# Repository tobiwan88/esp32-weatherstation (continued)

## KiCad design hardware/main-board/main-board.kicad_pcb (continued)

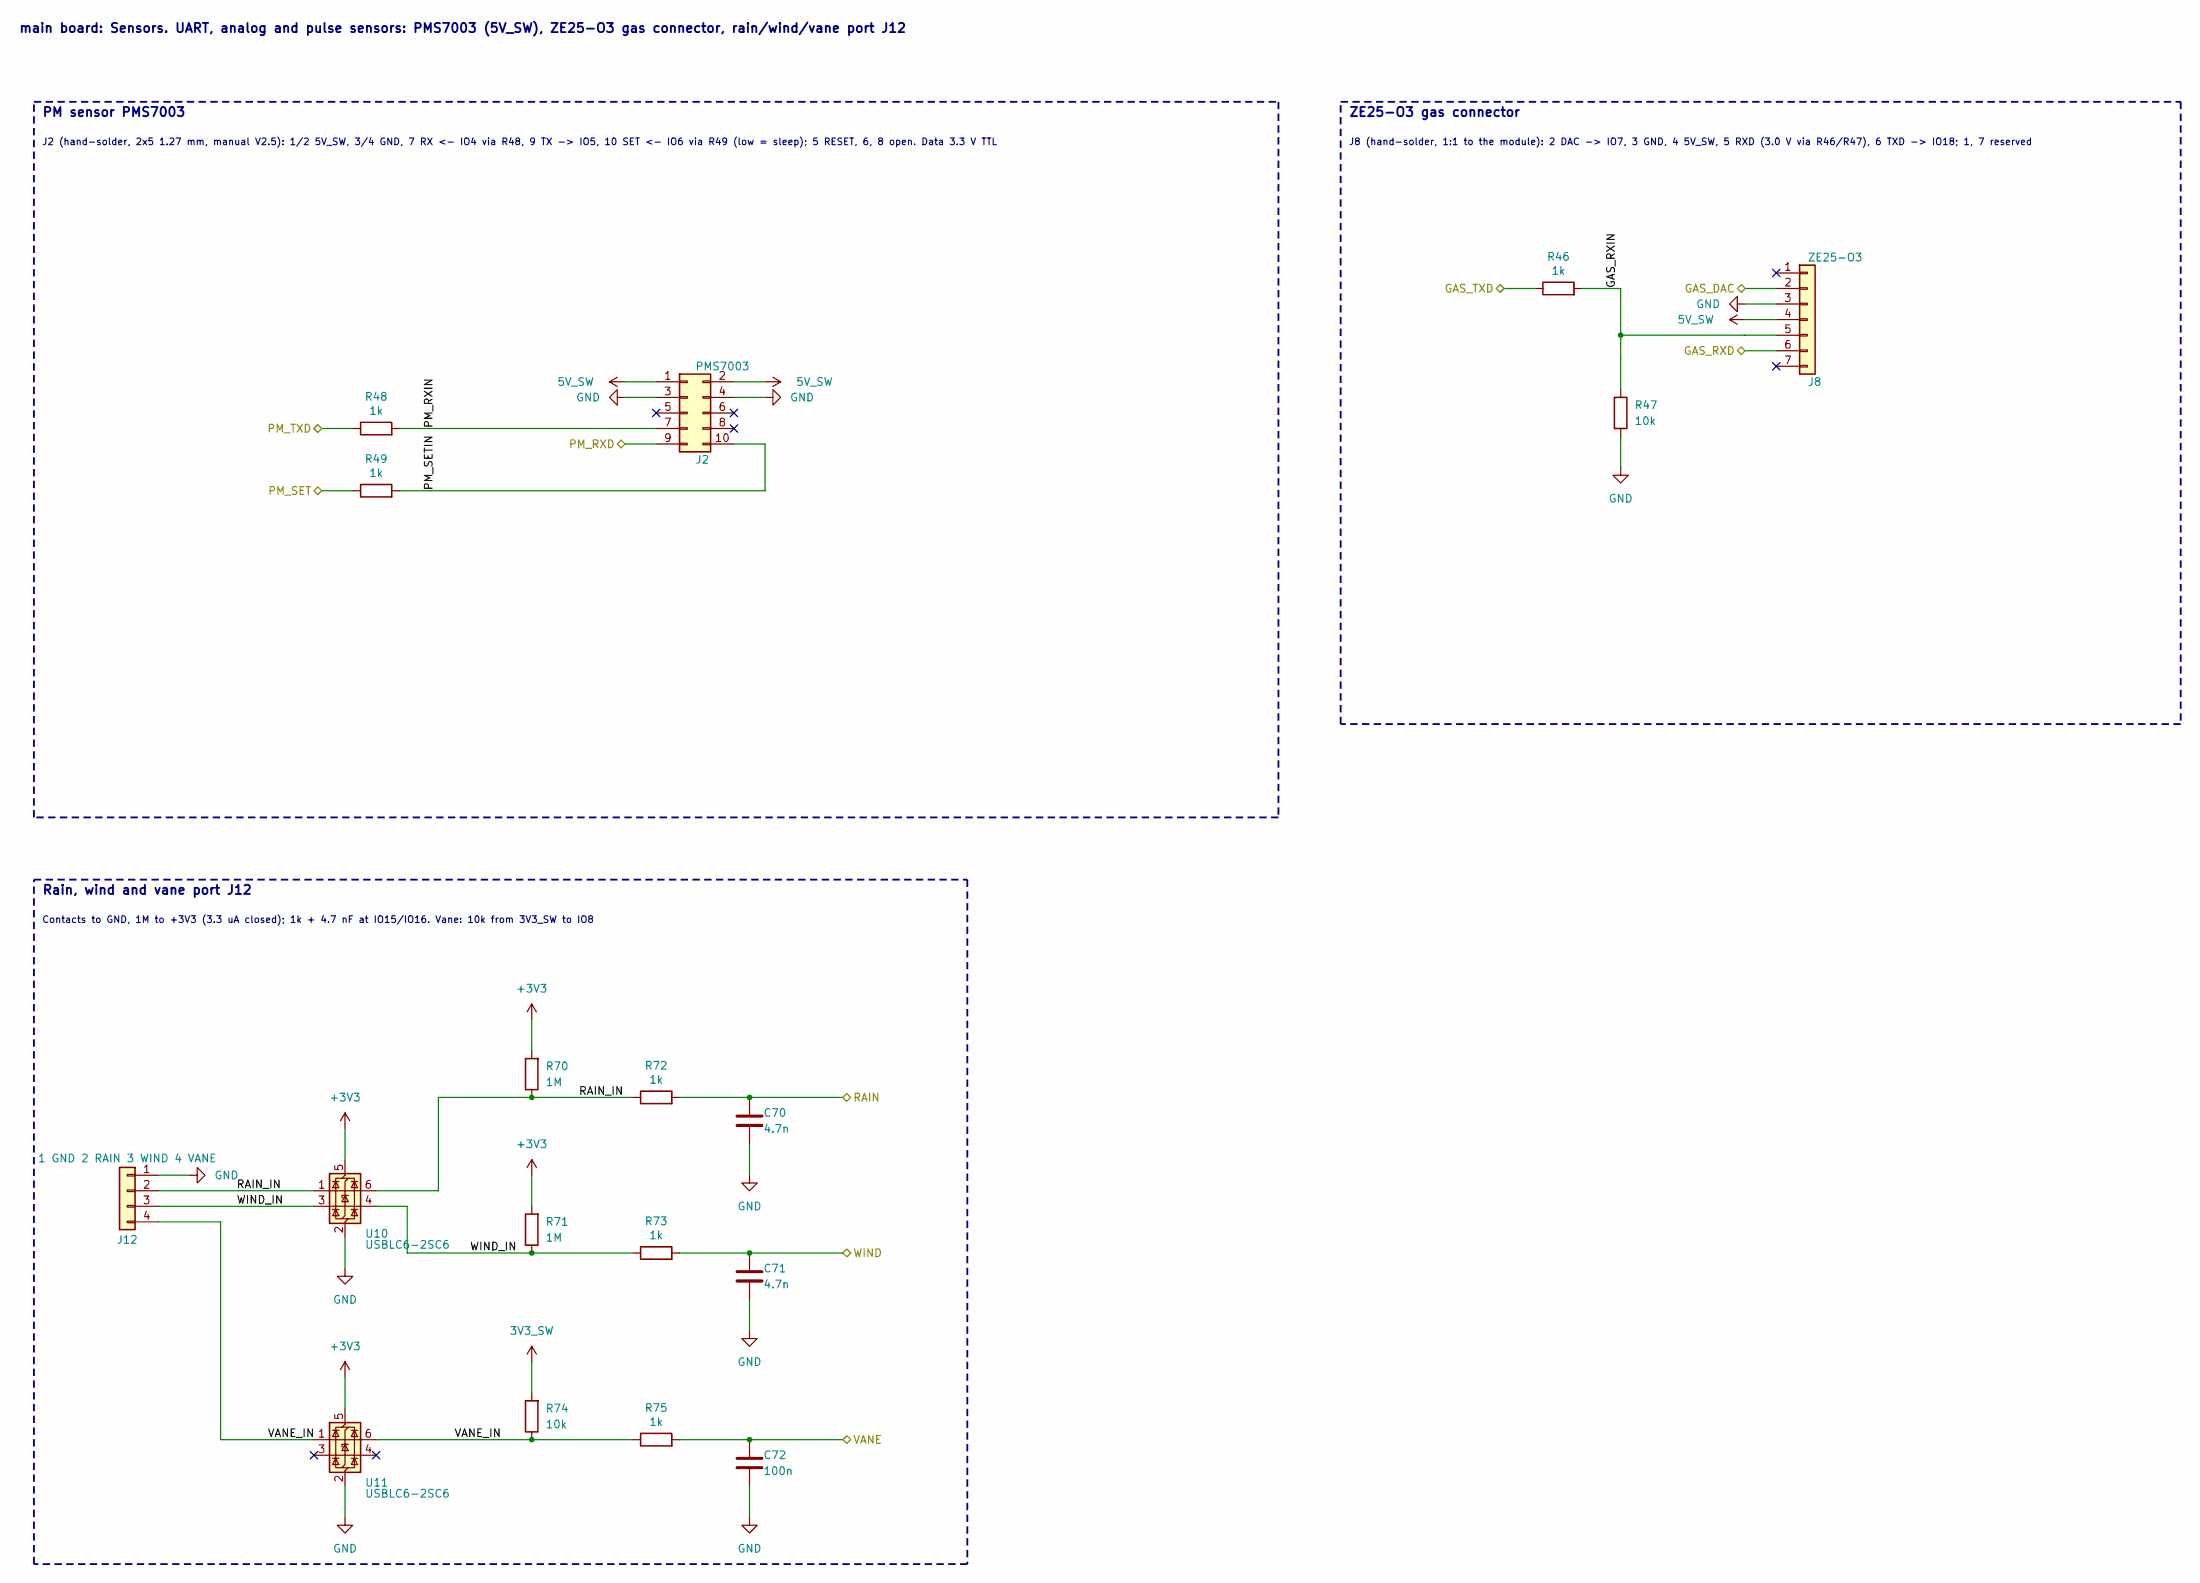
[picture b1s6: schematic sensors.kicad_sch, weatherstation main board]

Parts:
C70, C71: 4.7n; C_0402_1005Metric; LCSC C1538
C72: 100n; C_0402_1005Metric; LCSC C307331
J2: PMS7003; PinHeader_2x05_P1.27mm_Vertical
J8: ZE25-O3; JST_PH_B7B-PH-K_1x07_P2.00mm_Vertical
J12: 1 GND 2 RAIN 3 WIND 4 VANE; JST_PH_B4B-PH-K_1x04_P2.00mm_Vertical
R46, R48, R49, R72, R73, R75: 1k; R_0402_1005Metric; LCSC C11702
R47, R74: 10k; R_0402_1005Metric; LCSC C25744
R70, R71: 1M; R_0402_1005Metric; LCSC C26083
U10, U11: USBLC6-2SC6; SOT-23-6; LCSC C7519

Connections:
3V3_SW: R74.2; also elsewhere on the board
5V_SW: J2.1, J2.2, J8.4; also elsewhere on the board
+3V3: R70.2, R71.2, U10.5 (VBUS), U11.5 (VBUS); also elsewhere on the board
/MCU/GAS_DAC: J8.2; also elsewhere on the board
/MCU/GAS_RXD: J8.6; also elsewhere on the board
/MCU/GAS_TXD: R46.1; also elsewhere on the board
/MCU/PM_RXD: J2.9; also elsewhere on the board
/MCU/PM_SET: R49.1; also elsewhere on the board
/MCU/PM_TXD: R48.1; also elsewhere on the board
/MCU/RAIN: C70.1, R72.2; also elsewhere on the board
/MCU/VANE: C72.1, R75.2; also elsewhere on the board
/MCU/WIND: C71.1, R73.2; also elsewhere on the board
/Sensors/GAS_RXIN: J8.5, R46.2, R47.1
/Sensors/PM_RXIN: J2.7, R48.2
/Sensors/PM_SETIN: J2.10, R49.2
/Sensors/RAIN_IN: J12.2, R70.1, R72.1, U10.1 (I/O1), U10.6 (I/O1)
/Sensors/VANE_IN: J12.4, R74.1, R75.1, U11.1 (I/O1), U11.6 (I/O1)
/Sensors/WIND_IN: J12.3, R71.1, R73.1, U10.3 (I/O2), U10.4 (I/O2)
GND: C70.2, C71.2, C72.2, J2.3, J2.4, J8.3, J12.1, R47.2, U10.2 (GND), U11.2 (GND); also elsewhere on the board

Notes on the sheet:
PM sensor PMS7003
J2 (hand-solder, 2x5 1.27 mm, manual V2.5): 1/2 5V_SW, 3/4 GND, 7 RX <- IO4 via R48, 9 TX -> IO5, 10 SET <- IO6 via R49 (low = sleep); 5 RESET, 6, 8 open. Data 3.3 V TTL
ZE25-O3 gas connector
J8 (hand-solder, 1:1 to the module): 2 DAC -> IO7, 3 GND, 4 5V_SW, 5 RXD (3.0 V via R46/R47), 6 TXD -> IO18; 1, 7 reserved
Rain, wind and vane port J12
Contacts to GND, 1M to +3V3 (3.3 uA closed); 1k + 4.7 nF at IO15/IO16. Vane: 10k from 3V3_SW to IO8
main board: Sensors. UART, analog and pulse sensors: PMS7003 (5V_SW), ZE25-O3 gas connector, rain/wind/vane port J12

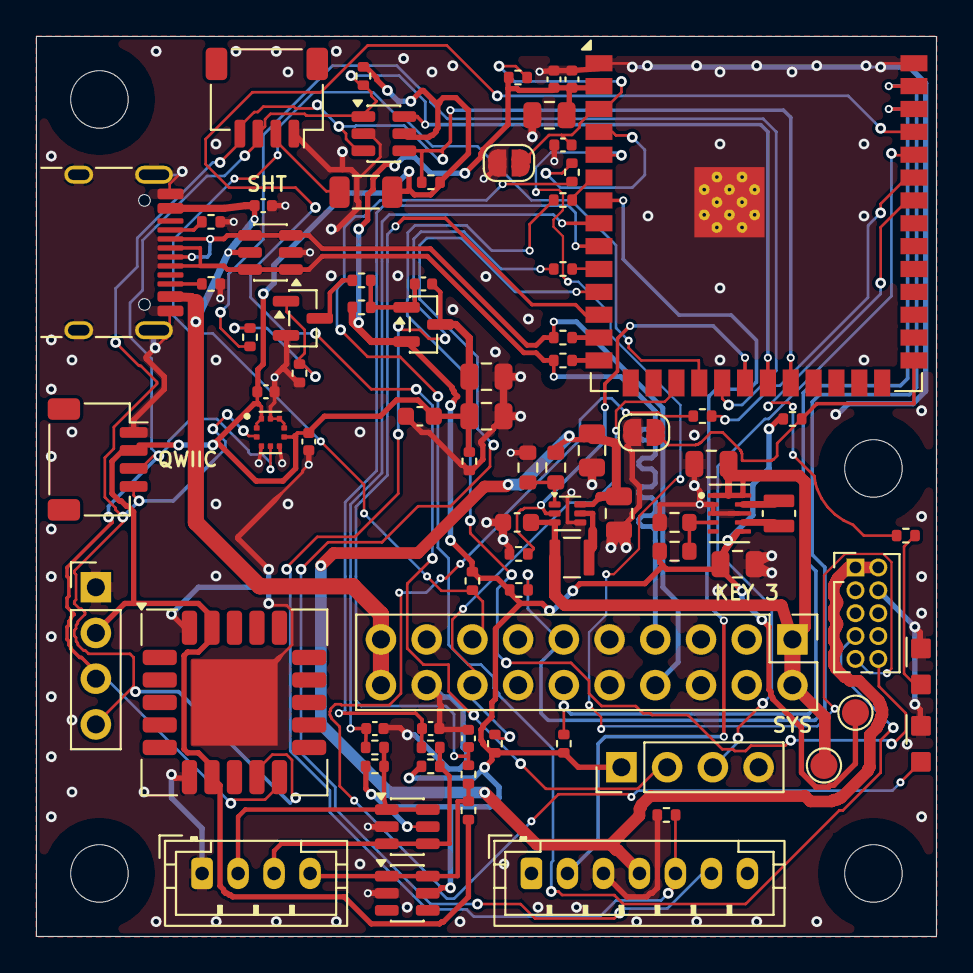
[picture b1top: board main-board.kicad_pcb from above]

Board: 4 copper layers, 50.0 x 50.0 mm, 86 parts (0 on the bottom side), 52 nets.

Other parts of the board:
H1, H2, H3, H4: MountingHole_3.2mm_M3_ISO7380

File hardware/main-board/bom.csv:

Comment,Designator,Footprint,Quantity,LCSC Part #,Class,Status,Function / notes
USB-C,J1,Connector_USB:USB_C_Receptacle_HRO_TYPE-C-31-M-12,1,C165948,Extended,VERIFIED LCSC part (class: boardgen.JLC_CLASS; stock: hw-check.sh --stock; datasheet values open),
USBLC6-2SC6,"U4,U5,U10,U11",Package_TO_SOT_SMD:SOT-23-6,4,C7519,Extended,VERIFIED LCSC part (class: boardgen.JLC_CLASS; stock: hw-check.sh --stock; datasheet values open),U4: USBLC6-2SC6 (USB); U5: USBLC6-2SC6 (I2C); U10: USBLC6-2SC6 (pulse); U11: USBLC6-2SC6 (vane)
5.1k,"R9,R10",Resistor_SMD:R_0402_1005Metric,2,C25905,Basic,VERIFIED LCSC part (class: boardgen.JLC_CLASS; stock: hw-check.sh --stock; datasheet values open),
J_PWR 2x10 key 3,J10,Connector_PinHeader_2.54mm:PinHeader_2x10_P2.54mm_Vertical,1,n/a,n/a,HAND-SOLDER,"J10: J_PWR 2x10 keyed 2.54 mm (main side: male pins, pin 3 pulled; hand-solder)"
1M,"R20,R70,R71",Resistor_SMD:R_0402_1005Metric,3,C26083,Basic,VERIFIED LCSC part (class: boardgen.JLC_CLASS; stock: hw-check.sh --stock; datasheet values open),
10k,"R22,R30,R31,R47,R54,R55,R74,R76",Resistor_SMD:R_0402_1005Metric,8,C25744,Basic,VERIFIED LCSC part (class: boardgen.JLC_CLASS; stock: hw-check.sh --stock; datasheet values open),R76: 10k (Q40 gate ramp)
ESP32-S3-WROOM-1-N8,U1,RF_Module:ESP32-S3-WROOM-1,1,C2913198,Extended,VERIFIED LCSC part (class: boardgen.JLC_CLASS; stock: hw-check.sh --stock; datasheet values open),
22u,"C30,C40,C41,C42,C43,C45,C46",Capacitor_SMD:C_0805_2012Metric,7,C45783,Basic,VERIFIED LCSC part (class: boardgen.JLC_CLASS; stock: hw-check.sh --stock; datasheet values open),C41: 22u (TPS63802 output: 22 uF per table 10-1); C45: 22u (boost output); C46: 22u (boost output)
100n,"C31,C35,C72,C90,C91",Capacitor_SMD:C_0402_1005Metric,5,C307331,Basic,VERIFIED LCSC part (class: boardgen.JLC_CLASS; stock: hw-check.sh --stock; datasheet values open),C35: 100n (USB_VBUS at J1)
1u,"C32,C33",Capacitor_SMD:C_0402_1005Metric,2,C52923,Basic,VERIFIED LCSC part (class: boardgen.JLC_CLASS; stock: hw-check.sh --stock; datasheet values open),
RESET,JP1,Jumper:SolderJumper-2_P1.3mm_Open_RoundedPad1.0x1.5mm,1,n/a,n/a,NOT ASSEMBLED,
BOOT,JP2,Jumper:SolderJumper-2_P1.3mm_Open_RoundedPad1.0x1.5mm,1,n/a,n/a,NOT ASSEMBLED,
22,"R32,R33",Resistor_SMD:R_0402_1005Metric,2,C25092,Basic,VERIFIED LCSC part (class: boardgen.JLC_CLASS; stock: hw-check.sh --stock; datasheet values open),
1k,"R34,R35,R41,R46,R48,R49,R72,R73,R75",Resistor_SMD:R_0402_1005Metric,9,C11702,Basic,VERIFIED LCSC part (class: boardgen.JLC_CLASS; stock: hw-check.sh --stock; datasheet values open),R46: 1k (GAS RXD level: 3.3 V x 10/11 = 3.0 V); R48: 1k (PM RX series); R49: 1k (PM SET series)
LED1 red side-view,"D10,D11",weatherstation:LED_LiteOn_LTST-S270_SideView,2,C125114,Extended,VERIFIED LCSC part (class: boardgen.JLC_CLASS; stock: hw-check.sh --stock; datasheet values open),D10: LED1 red side-view (LTST-S270KRKT); D11: LED2 red side-view (LTST-S270KRKT)
DEBUG UART (pin 1 3V3 only),J7,Connector_PinHeader_2.54mm:PinHeader_1x04_P2.54mm_Vertical,1,n/a,n/a,HAND-SOLDER,J7: DEBUG UART (1 = 3.3 V only)
TPS63802,U2,weatherstation:TPS63802_DLA_VSON-HR-10_2x3mm,1,C2845237,Extended,VERIFIED LCSC part (class: boardgen.JLC_CLASS; stock: hw-check.sh --stock; datasheet values open),U2: TPS63802DLA 3.3 V buck-boost
0.47uH,L4,weatherstation:L_Sunlord_WPN201610H,1,C97009,Extended,VERIFIED LCSC part (class: boardgen.JLC_CLASS; stock: hw-check.sh --stock; datasheet values open),"L4: 0.47uH (Sunlord WPN201610HR47MT: Isat 4.0 A max, Irms 2.7 A)"
220k 1%,R52,Resistor_SMD:R_0603_1608Metric,1,C22961,Basic,VERIFIED LCSC part (class: boardgen.JLC_CLASS; stock: hw-check.sh --stock; datasheet values open),R52: 220k 1% (FB top: 0.5 V x (1 + 220k/39k) = 3.32 V)
39k 1%,R53,Resistor_SMD:R_0603_1608Metric,1,C23153,Basic,VERIFIED LCSC part (class: boardgen.JLC_CLASS; stock: hw-check.sh --stock; datasheet values open),"R53: 39k 1% (FB bottom, datasheet max 100k)"
AO3401A,Q40,Package_TO_SOT_SMD:SOT-23,1,C15127,Basic,VERIFIED LCSC part (class: boardgen.JLC_CLASS; stock: hw-check.sh --stock; datasheet values open),Q40: AO3401A 3V3_SW switch
100k,"R40,R42,R45",Resistor_SMD:R_0402_1005Metric,3,C25741,Basic,VERIFIED LCSC part (class: boardgen.JLC_CLASS; stock: hw-check.sh --stock; datasheet values open),R45: 100k (EN pull-down: boost off by default)
22n,C48,Capacitor_SMD:C_0402_1005Metric,1,C1532,Basic,VERIFIED LCSC part (class: boardgen.JLC_CLASS; stock: hw-check.sh --stock; datasheet values open),C48: 22n (Q40 gate-drain ramp)
2N7002,Q41,Package_TO_SOT_SMD:SOT-23,1,C8545,Basic,VERIFIED LCSC part (class: boardgen.JLC_CLASS; stock: hw-check.sh --stock; datasheet values open),Q41: 2N7002 (sensor enable)
22k,R78,Resistor_SMD:R_0402_1005Metric,1,C25768,Basic,VERIFIED LCSC part (class: boardgen.JLC_CLASS; stock: hw-check.sh --stock; datasheet values open),R78: 22k (3V3_SW bleed)
TPS61023,U7,Package_TO_SOT_SMD:SOT-563,1,C919459,Extended,VERIFIED LCSC part (class: boardgen.JLC_CLASS; stock: hw-check.sh --stock; datasheet values open),U7: TPS61023DRLR 5 V boost
1uH,L5,weatherstation:L_TDK_VLS252010,1,C88211,Extended,VERIFIED LCSC part (class: boardgen.JLC_CLASS; stock: hw-check.sh --stock; datasheet values open),"L5: 1uH (VLS252010HBX-1R0M-1, same as L1)"
510k 1%,R43,Resistor_SMD:R_0603_1608Metric,1,C23192,Basic,VERIFIED LCSC part (class: boardgen.JLC_CLASS; stock: hw-check.sh --stock; datasheet values open),R43: 510k 1% (boost FB top: 0.595 V x (1 + 510k/68k) = 5.06 V)
68k 1%,R44,Resistor_SMD:R_0603_1608Metric,1,C23231,Basic,VERIFIED LCSC part (class: boardgen.JLC_CLASS; stock: hw-check.sh --stock; datasheet values open),R44: 68k 1% (boost FB bottom)
10u,C44,Capacitor_SMD:C_0603_1608Metric,1,C19702,Basic,VERIFIED LCSC part (class: boardgen.JLC_CLASS; stock: hw-check.sh --stock; datasheet values open),C44: 10u (boost input)
PMS7003,J2,Connector_PinHeader_1.27mm:PinHeader_2x05_P1.27mm_Vertical,1,n/a,n/a,HAND-SOLDER,J2: PMS7003 (2x5 1.27 mm)
SCD41 DNP,U8,Sensor:Sensirion_SCD4x-1EP_10.1x10.1mm_P1.25mm_EP4.8x4.8mm,1,n/a,n/a,NOT ASSEMBLED,U8: SCD41 DNP (C3659294)
10u DNP,C47,Capacitor_SMD:C_0603_1608Metric,1,n/a,n/a,NOT ASSEMBLED,"C47: 10u DNP (C19702; SCD41 VDD, fit with U8)"
SHT head cable,"J3,J4",Connector_JST:JST_SH_SM04B-SRSS-TB_1x04-1MP_P1.00mm_Horizontal,2,C160404,Extended,VERIFIED LCSC part (class: boardgen.JLC_CLASS; stock: hw-check.sh --stock; datasheet values open),J3: SHT head cable (Qwiic); J4: Qwiic 2
100 1206,R77,Resistor_SMD:R_1206_3216Metric,1,C17901,Basic,VERIFIED LCSC part (class: boardgen.JLC_CLASS; stock: hw-check.sh --stock; datasheet values open),R77: 100 1206 (outdoor cable feed)
2.2k,"R50,R51",Resistor_SMD:R_0402_1005Metric,2,C25879,Basic,VERIFIED LCSC part (class: boardgen.JLC_CLASS; stock: hw-check.sh --stock; datasheet values open),
ZE25-O3,J8,Connector_JST:JST_PH_B7B-PH-K_1x07_P2.00mm_Vertical,1,n/a,n/a,HAND-SOLDER,J8: ZE25-O3 (cable pitch to confirm)
BMP580,U9,weatherstation:Bosch_LGA-10_2x2mm,1,C22391138,Extended,"LCSC part VERIFIED (BMP580, C22391138); pin-out UNVERIFIED for the BMP580: no public BMP580 datasheet, land pattern and pins from the BMP581 datasheet BST-BMP581-DS004-13 (same LGA-10 2x2 package)",U9: BMP580 (0x46)
I2C 2.54 (GND 3V3 SDA SCL),J11,Connector_PinHeader_2.54mm:PinHeader_1x04_P2.54mm_Vertical,1,n/a,n/a,HAND-SOLDER,J11: I2C 2.54 (GND 3V3_SW SDA SCL)
1 GND 2 RAIN 3 WIND 4 VANE,J12,Connector_JST:JST_PH_B4B-PH-K_1x04_P2.00mm_Vertical,1,n/a,n/a,HAND-SOLDER,J12: RAIN/WIND (1 GND 2 RAIN 3 WIND 4 VANE)
4.7n,"C70,C71",Capacitor_SMD:C_0402_1005Metric,2,C1538,Basic,VERIFIED LCSC part (class: boardgen.JLC_CLASS; stock: hw-check.sh --stock; datasheet values open),
Test points,"TP1,TP2",TestPoint:TestPoint_Pad_D1.5mm,2,n/a,n/a,PCB pads only,SYS/3V3 test pads

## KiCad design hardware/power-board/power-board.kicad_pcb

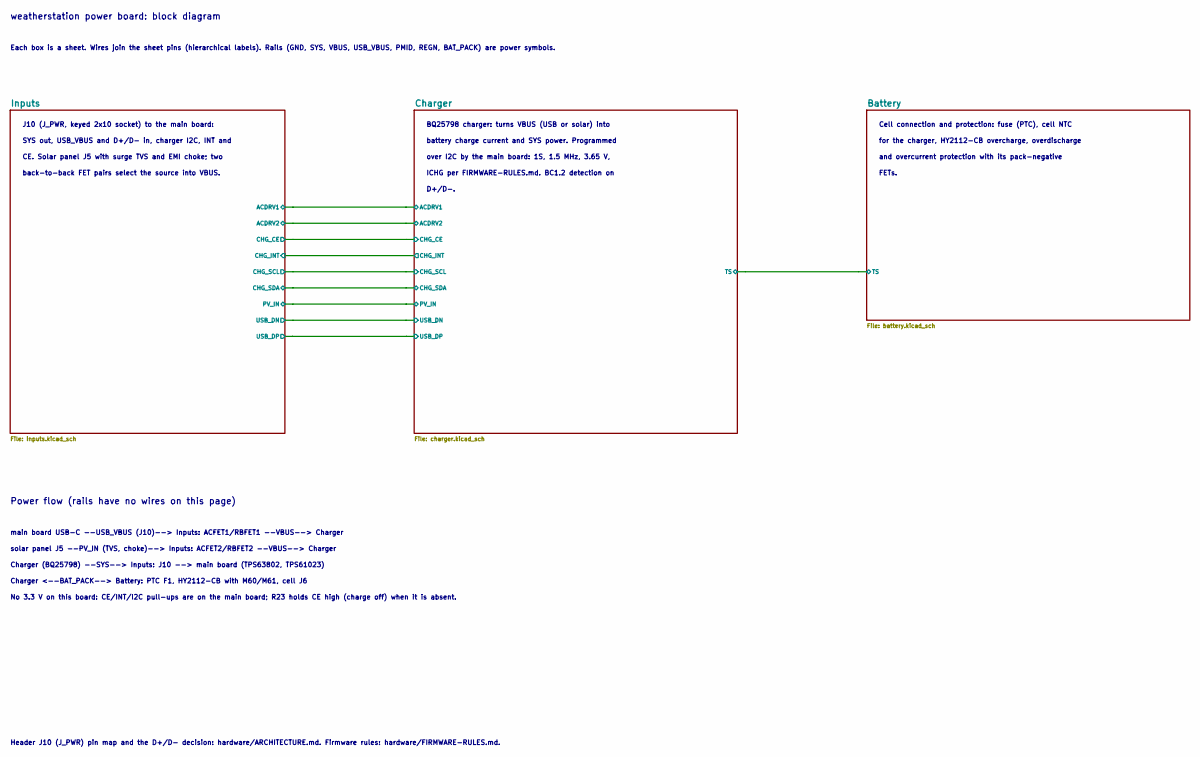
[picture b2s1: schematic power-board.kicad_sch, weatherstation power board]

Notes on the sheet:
weatherstation power board: block diagram
Each box is a sheet. Wires join the sheet pins (hierarchical labels). Rails (GND, SYS, VBUS, USB_VBUS, PMID, REGN, BAT_PACK) are power symbols.
Power flow (rails have no wires on this page)
main board USB-C --USB_VBUS (J10)--> Inputs: ACFET1/RBFET1 --VBUS--> Charger
solar panel J5 --PV_IN (TVS, choke)--> Inputs: ACFET2/RBFET2 --VBUS--> Charger
Charger (BQ25798) --SYS--> Inputs: J10 --> main board (TPS63802, TPS61023)
Charger <--BAT_PACK--> Battery: PTC F1, HY2112-CB with M60/M61, cell J6
No 3.3 V on this board: CE/INT/I2C pull-ups are on the main board; R23 holds CE high (charge off) when it is absent.
Header J10 (J_PWR) pin map and the D+/D- decision: hardware/ARCHITECTURE.md. Firmware rules: hardware/FIRMWARE-RULES.md.
J10 (J_PWR, keyed 2x10 socket) to the main board:
SYS out, USB_VBUS and D+/D- in, charger I2C, INT and
CE. Solar panel J5 with surge TVS and EMI choke; two
back-to-back FET pairs select the source into VBUS.
BQ25798 charger: turns VBUS (USB or solar) into
battery charge current and SYS power. Programmed
over I2C by the main board: 1S, 1.5 MHz, 3.65 V,
ICHG per FIRMWARE-RULES.md. BC1.2 detection on
D+/D-.
Cell connection and protection: fuse (PTC), cell NTC
for the charger, HY2112-CB overcharge, overdischarge
and overcurrent protection with its pack-negative
FETs.

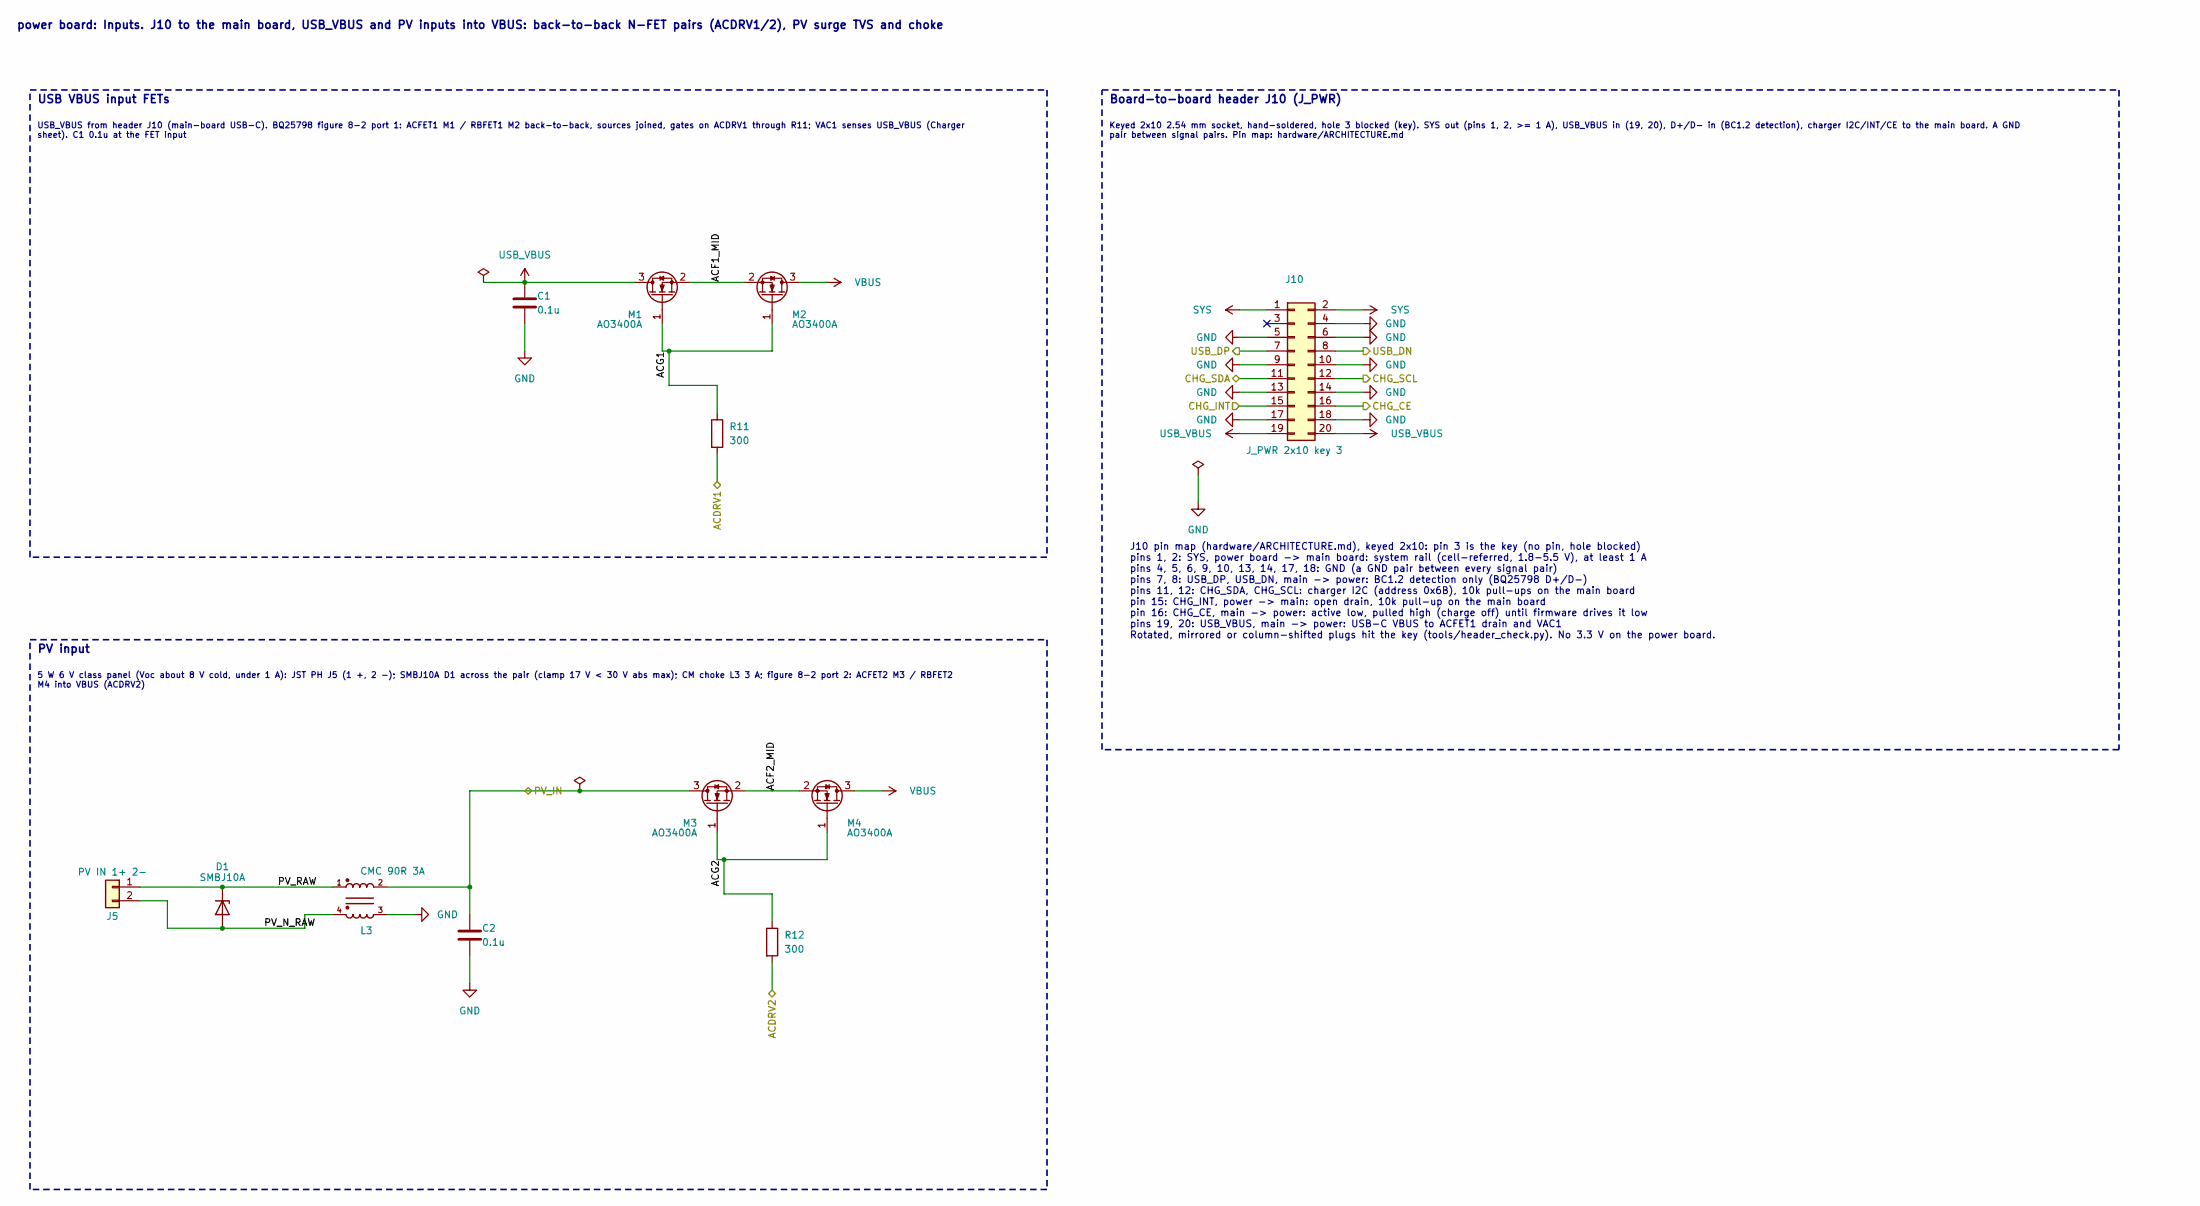
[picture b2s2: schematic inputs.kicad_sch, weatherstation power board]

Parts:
C1, C2: 0.1u; C_0402_1005Metric; LCSC C307331
D1: SMBJ10A; D_SMB; LCSC C151250
J5: PV IN 1+ 2-; JST_PH_B2B-PH-K_1x02_P2.00mm_Vertical
J10: J_PWR 2x10 key 3; PinHeader_2x10_P2.54mm_Vertical
L3: CMC 90R 3A; CMF4532F_4P; LCSC C963746
M1, M2, M3, M4: AO3400A; SOT-23; LCSC C20917
R11, R12: 300; R_0603_1608Metric; LCSC C23025

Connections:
/Charger/ACDRV1: R11.2; also elsewhere on the board
/Charger/ACDRV2: R12.2; also elsewhere on the board
/Charger/CHG_CE: J10.16; also elsewhere on the board
/Charger/CHG_INT: J10.15; also elsewhere on the board
/Charger/CHG_SCL: J10.12; also elsewhere on the board
/Charger/CHG_SDA: J10.11; also elsewhere on the board
/Charger/PV_IN: C2.1, L3.2, M3.3 (D); also elsewhere on the board
/Charger/USB_DN: J10.8; also elsewhere on the board
/Charger/USB_DP: J10.7; also elsewhere on the board
/Inputs/ACF1_MID: M1.2 (S), M2.2 (S)
/Inputs/ACF2_MID: M3.2 (S), M4.2 (S)
/Inputs/ACG1: M1.1 (G), M2.1 (G), R11.1
/Inputs/ACG2: M3.1 (G), M4.1 (G), R12.1
/Inputs/PV_N_RAW: D1.2 (A), J5.2, L3.4
/Inputs/PV_RAW: D1.1 (K), J5.1, L3.1
GND: C1.2, C2.2, J10.4, J10.5, J10.6, J10.9, J10.10, J10.13, J10.14, J10.17, J10.18, L3.3; also elsewhere on the board
SYS: J10.1, J10.2; also elsewhere on the board
USB_VBUS: C1.1, J10.19, J10.20, M1.3 (D); also elsewhere on the board
VBUS: M2.3 (D), M4.3 (D); also elsewhere on the board

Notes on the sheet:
USB VBUS input FETs
USB_VBUS from header J10 (main-board USB-C). BQ25798 figure 8-2 port 1: ACFET1 M1 / RBFET1 M2 back-to-back, sources joined, gates on ACDRV1 through R11; VAC1 senses USB_VBUS (Charger sheet). C1 0.1u at the FET input
PV input
5 W 6 V class panel (Voc about 8 V cold, under 1 A): JST PH J5 (1 +, 2 -); SMBJ10A D1 across the pair (clamp 17 V < 30 V abs max); CM choke L3 3 A; figure 8-2 port 2: ACFET2 M3 / RBFET2 M4 into VBUS (ACDRV2)
Board-to-board header J10 (J_PWR)
Keyed 2x10 2.54 mm socket, hand-soldered, hole 3 blocked (key). SYS out (pins 1, 2, >= 1 A), USB_VBUS in (19, 20), D+/D- in (BC1.2 detection), charger I2C/INT/CE to the main board. A GND pair between signal pairs. Pin map: hardware/ARCHITECTURE.md
J10 pin map (hardware/ARCHITECTURE.md), keyed 2x10: pin 3 is the key (no pin, hole blocked) pins 1, 2: SYS, power board -> main board: system rail (cell-referred, 1.8-5.5 V), at least 1 A pins 4, 5, 6, 9, 10, 13, 14, 17, 18: GND (a GND pair between every signal pair) pins 7, 8: USB_DP, USB_DN, main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
power board: Inputs. J10 to the main board, USB_VBUS and PV inputs into VBUS: back-to-back N-FET pairs (ACDRV1/2), PV surge TVS and choke

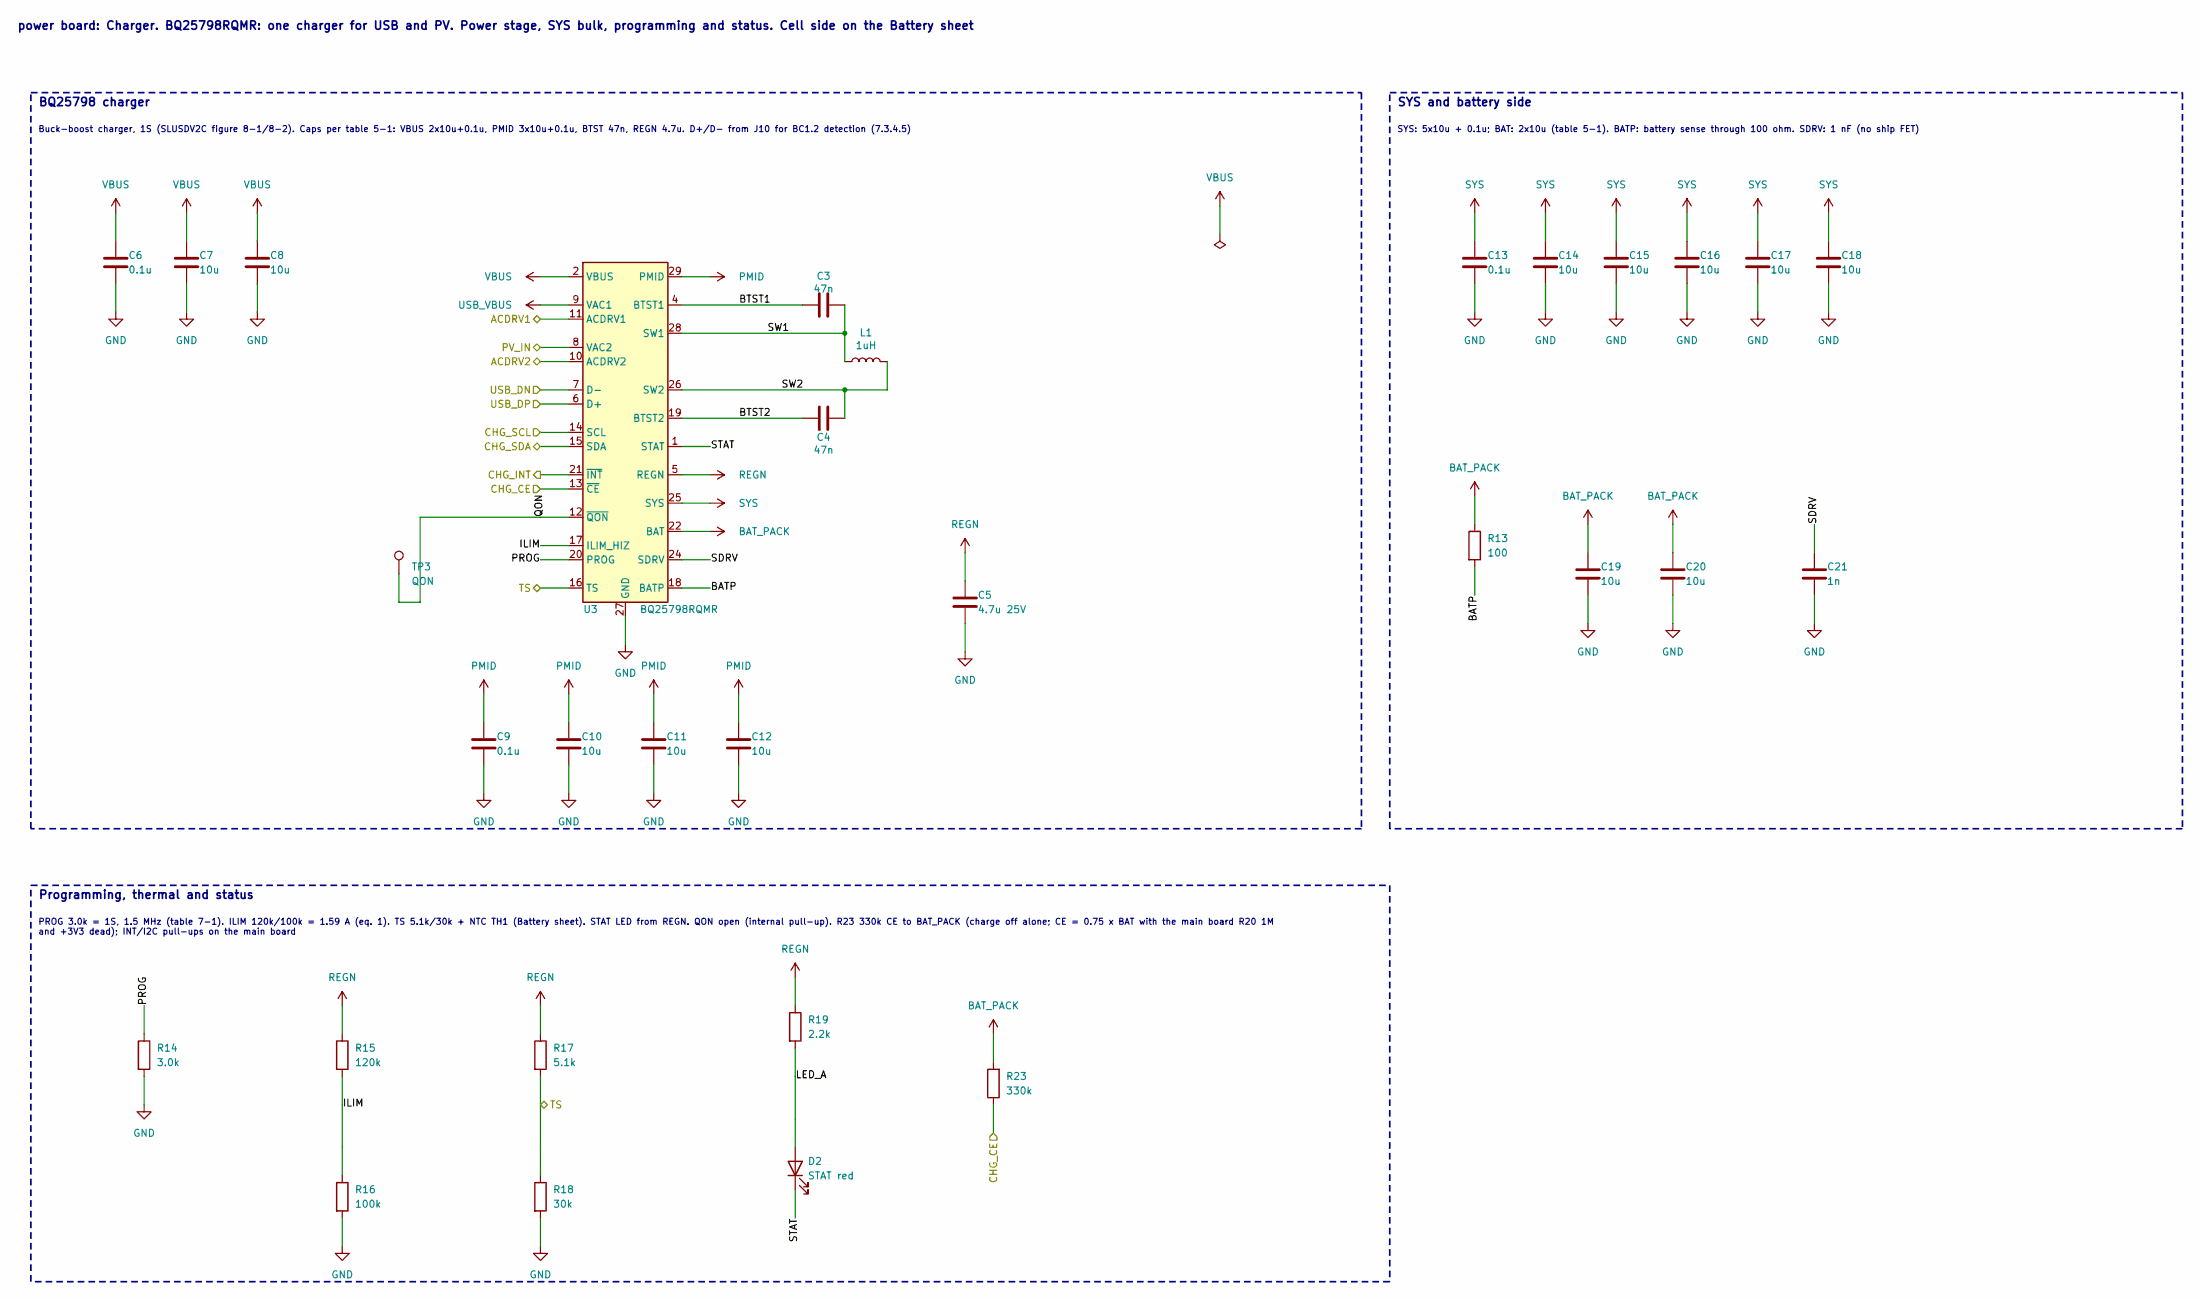
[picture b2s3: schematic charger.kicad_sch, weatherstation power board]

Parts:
C3, C4: 47n; C_0603_1608Metric; LCSC C1622
C5: 4.7u 25V; C_0805_2012Metric; LCSC C1779
C6, C9, C13: 0.1u; C_0402_1005Metric; LCSC C307331
C7, C8, C10, C11, C12, C14, C15, C16, C17, C18, C19, C20: 10u; C_0805_2012Metric; LCSC C15850
C21: 1n; C_0402_1005Metric; LCSC C1523
D2: STAT red; LED_0603_1608Metric; LCSC C2286
L1: 1uH; L_TDK_VLS252010; LCSC C88211
R13: 100; R_0402_1005Metric; LCSC C25076
R14: 3.0k; R_0603_1608Metric; LCSC C4211
R15: 120k; R_0603_1608Metric; LCSC C25808
R16: 100k; R_0402_1005Metric; LCSC C25741
R17: 5.1k; R_0402_1005Metric; LCSC C25905
R18: 30k; R_0603_1608Metric; LCSC C22984
R19: 2.2k; R_0402_1005Metric; LCSC C25879
R23: 330k; R_0402_1005Metric; LCSC C25778
TP3: QON; TestPoint_Pad_D1.5mm
U3: BQ25798RQMR; Texas_RQM0029A_VQFN-29_4x4mm_P0.4mm; LCSC C2876593

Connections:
/Battery/TS: R17.2, R18.1, U3.16 (TS); also elsewhere on the board
/Charger/ACDRV1: U3.11 (ACDRV1); also elsewhere on the board
/Charger/ACDRV2: U3.10 (ACDRV2); also elsewhere on the board
/Charger/BATP: R13.2, U3.18 (BATP)
/Charger/BTST1: C3.1, U3.4 (BTST1)
/Charger/BTST2: C4.1, U3.19 (BTST2)
/Charger/CHG_CE: R23.1, U3.13 (~CE); also elsewhere on the board
/Charger/CHG_INT: U3.21 (~INT); also elsewhere on the board
/Charger/CHG_SCL: U3.14 (SCL); also elsewhere on the board
/Charger/CHG_SDA: U3.15 (SDA); also elsewhere on the board
/Charger/ILIM: R15.2, R16.1, U3.17 (ILIM_HIZ)
/Charger/LED_A: D2.2 (A), R19.2
/Charger/PROG: R14.1, U3.20 (PROG)
/Charger/PV_IN: U3.8 (VAC2); also elsewhere on the board
/Charger/QON: TP3.1, U3.12 (~QON)
/Charger/SDRV: C21.1, U3.24 (SDRV)
/Charger/STAT: D2.1 (K), U3.1 (STAT)
/Charger/SW1: C3.2, L1.1, U3.28 (SW1)
/Charger/SW2: C4.2, L1.2, U3.26 (SW2)
/Charger/USB_DN: U3.7 (D-); also elsewhere on the board
/Charger/USB_DP: U3.6 (D+); also elsewhere on the board
BAT_PACK: C19.1, C20.1, R13.1, R23.2, U3.22 (BAT), U3.23 (BAT); also elsewhere on the board
GND: C5.2, C6.2, C7.2, C8.2, C9.2, C10.2, C11.2, C12.2, C13.2, C14.2, C15.2, C16.2, C17.2, C18.2, C19.2, C20.2, C21.2, R14.2, R16.2, R18.2, U3.27 (GND); also elsewhere on the board
PMID: C9.1, C10.1, C11.1, C12.1, U3.29 (PMID)
REGN: C5.1, R15.1, R17.1, R19.1, U3.5 (REGN)
SYS: C13.1, C14.1, C15.1, C16.1, C17.1, C18.1, U3.25 (SYS); also elsewhere on the board
USB_VBUS: U3.9 (VAC1); also elsewhere on the board
VBUS: C6.1, C7.1, C8.1, U3.2 (VBUS), U3.3 (VBUS); also elsewhere on the board

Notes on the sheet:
BQ25798 charger
Buck-boost charger, 1S (SLUSDV2C figure 8-1/8-2). Caps per table 5-1: VBUS 2x10u+0.1u, PMID 3x10u+0.1u, BTST 47n, REGN 4.7u. D+/D- from J10 for BC1.2 detection (7.3.4.5)
SYS and battery side
SYS: 5x10u + 0.1u; BAT: 2x10u (table 5-1). BATP: battery sense through 100 ohm. SDRV: 1 nF (no ship FET)
Programming, thermal and status
PROG 3.0k = 1S, 1.5 MHz (table 7-1). ILIM 120k/100k = 1.59 A (eq. 1). TS 5.1k/30k + NTC TH1 (Battery sheet). STAT LED from REGN. QON open (internal pull-up). R23 330k CE to BAT_PACK (charge off alone; CE = 0.75 x BAT with the main board R20 1M and +3V3 dead); INT/I2C pull-ups on the main board
power board: Charger. BQ25798RQMR: one charger for USB and PV. Power stage, SYS bulk, programming and status. Cell side on the Battery sheet

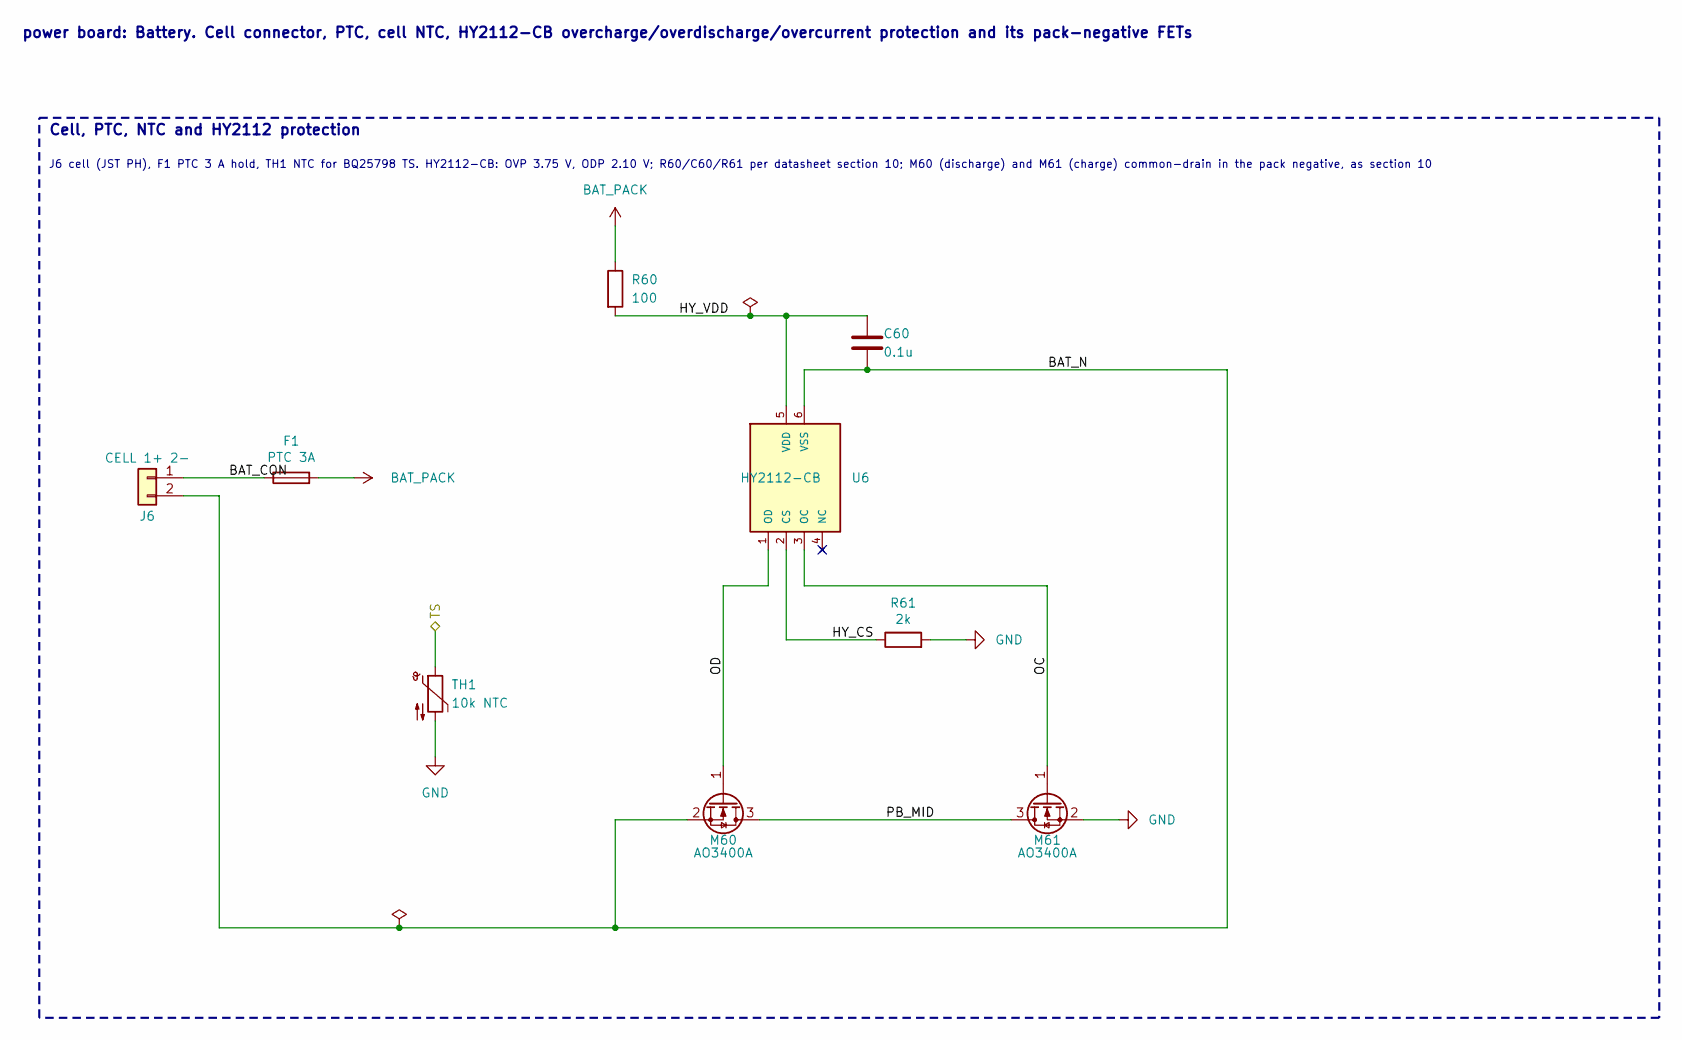
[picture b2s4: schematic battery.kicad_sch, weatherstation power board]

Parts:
C60: 0.1u; C_0402_1005Metric; LCSC C307331
F1: PTC 3A; Fuse_1812_4532Metric; LCSC C21004
J6: CELL 1+ 2-; JST_PH_B2B-PH-K_1x02_P2.00mm_Vertical
M60, M61: AO3400A; SOT-23; LCSC C20917
R60: 100; R_0402_1005Metric; LCSC C25076
R61: 2k; R_0402_1005Metric; LCSC C4109
TH1: 10k NTC; R_0603_1608Metric; LCSC C13564
U6: HY2112-CB; SOT-23-6; LCSC C168764

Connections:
/Battery/BAT_CON: F1.1, J6.1
/Battery/BAT_N: C60.2, J6.2, M60.2 (S), U6.6 (VSS)
/Battery/HY_CS: R61.1, U6.2 (CS)
/Battery/HY_VDD: C60.1, R60.2, U6.5 (VDD)
/Battery/OC: M61.1 (G), U6.3 (OC)
/Battery/OD: M60.1 (G), U6.1 (OD)
/Battery/PB_MID: M60.3 (D), M61.3 (D)
/Battery/TS: TH1.1; also elsewhere on the board
BAT_PACK: F1.2, R60.1; also elsewhere on the board
GND: M61.2 (S), R61.2, TH1.2; also elsewhere on the board

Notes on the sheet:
Cell, PTC, NTC and HY2112 protection
J6 cell (JST PH), F1 PTC 3 A hold, TH1 NTC for BQ25798 TS. HY2112-CB: OVP 3.75 V, ODP 2.10 V; R60/C60/R61 per datasheet section 10; M60 (discharge) and M61 (charge) common-drain in the pack negative, as section 10
power board: Battery. Cell connector, PTC, cell NTC, HY2112-CB overcharge/overdischarge/overcurrent protection and its pack-negative FETs
